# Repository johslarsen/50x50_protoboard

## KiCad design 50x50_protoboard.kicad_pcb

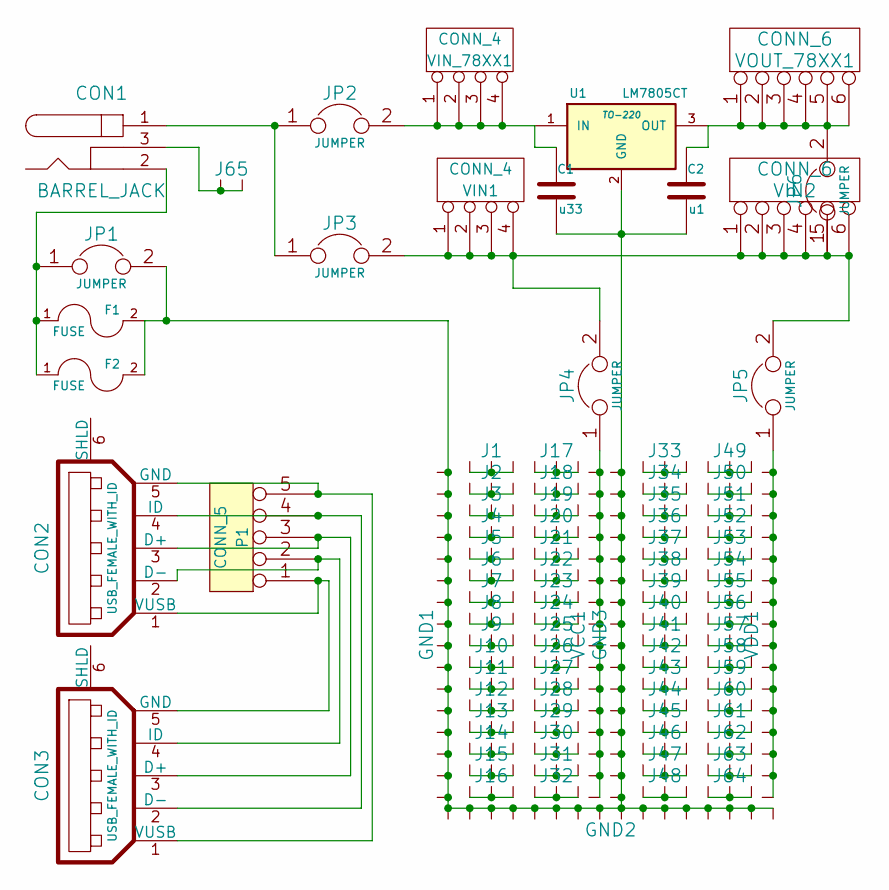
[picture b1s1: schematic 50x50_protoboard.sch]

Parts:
C1: u33
C2: u1
CON1: BARREL_JACK
CON2, CON3: USB_FEMALE_WITH_ID
F1, F2: FUSE
GND1, GND2, GND3: INTERCONNECT_16X1
J1, J2, J3, J4, J5, J6, J7, J8, J9, J10, J11, J12, J13, J14, J15, J16, J17, J18, J19, J20, J21, J22, J23, J24, J25, J26, J27, J28, J29, J30, J31, J32, J33, J34, J35, J36, J37, J38, J39, J40, J41, J42, J43, J44, J45, J46, J47, J48, J49, J50, J51, J52, J53, J54, J55, J56, J57, J58, J59, J60, J61, J62, J63, J64: INTERCONNECT_3X1
J65: INTERCONNECT_2X1
JP1, JP2, JP3, JP4, JP5, JP6: JUMPER
P1: CONN_5
U1: LM7805CT; TO-220
VCC1: INTERCONNECT_16X1
VDD1: INTERCONNECT_16X1
VIN1: CONN_4
VIN2: CONN_6
VIN_78XX1: CONN_4
VOUT_78XX1: CONN_6

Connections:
unnamed: C1.1, JP2.2, U1.1 (IN), VIN_78XX1.1, VIN_78XX1.2, VIN_78XX1.3, VIN_78XX1.4
unnamed: C1.2, C2.2, F1.2, F2.2, GND1.1, GND2.1, GND3.1, JP1.2, U1.2 (GND)
unnamed: C2.1, JP6.2, U1.3 (OUT), VOUT_78XX1.1, VOUT_78XX1.2, VOUT_78XX1.3, VOUT_78XX1.4, VOUT_78XX1.5, VOUT_78XX1.6
unnamed: CON1.1, JP2.1, JP3.1
unnamed: CON1.2, F1.1, F2.1, JP1.1
unnamed: CON1.3, J65.1
unnamed: CON2.1 (VUSB), CON3.5 (GND), P1.1
unnamed: CON2.2 (D-), CON3.4 (ID), P1.2
unnamed: CON2.3 (D+), CON3.3 (D+), P1.3
unnamed: CON2.4 (ID), CON3.2 (D-), P1.4
unnamed: CON2.5 (GND), CON3.1 (VUSB), P1.5
unnamed: JP3.2, JP4.2, JP5.2, JP6.1, VIN1.1, VIN1.2, VIN1.3, VIN1.4, VIN2.1, VIN2.2, VIN2.3, VIN2.4, VIN2.5, VIN2.6
unnamed: JP4.1, VCC1.1
unnamed: JP5.1, VDD1.1

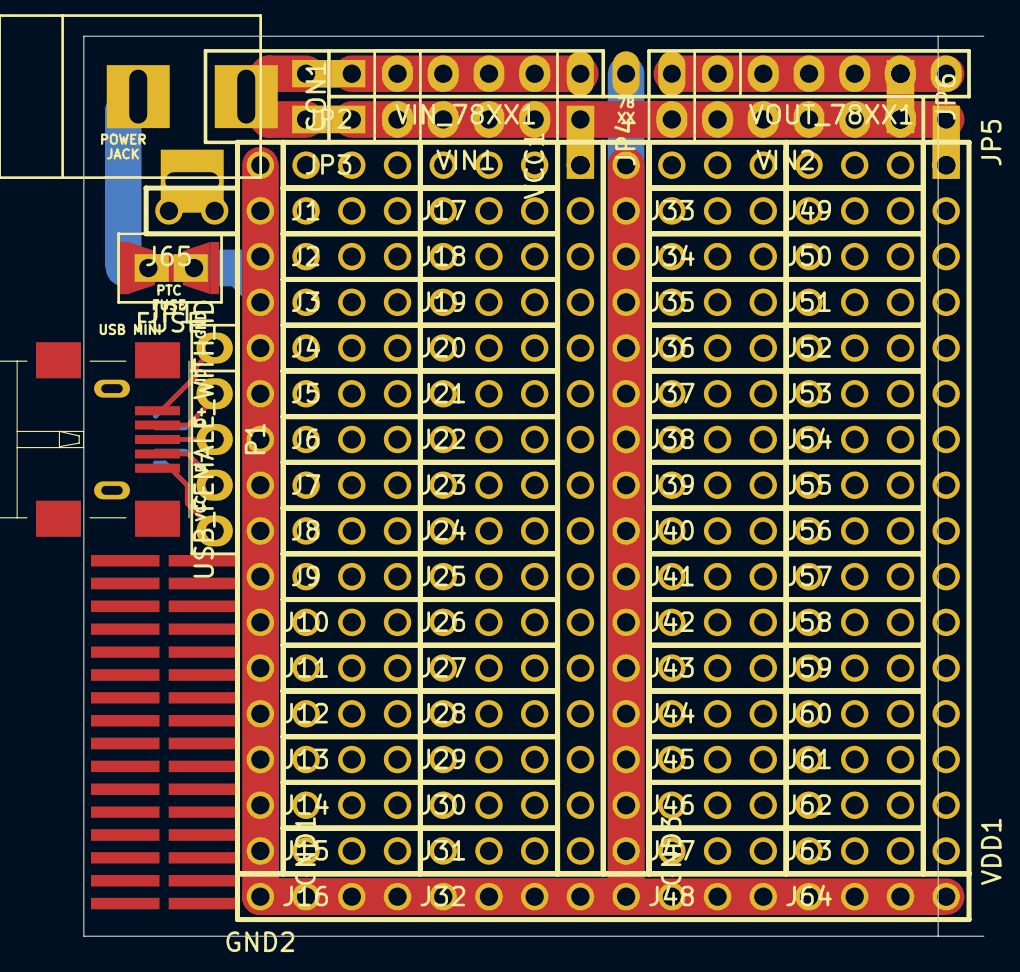
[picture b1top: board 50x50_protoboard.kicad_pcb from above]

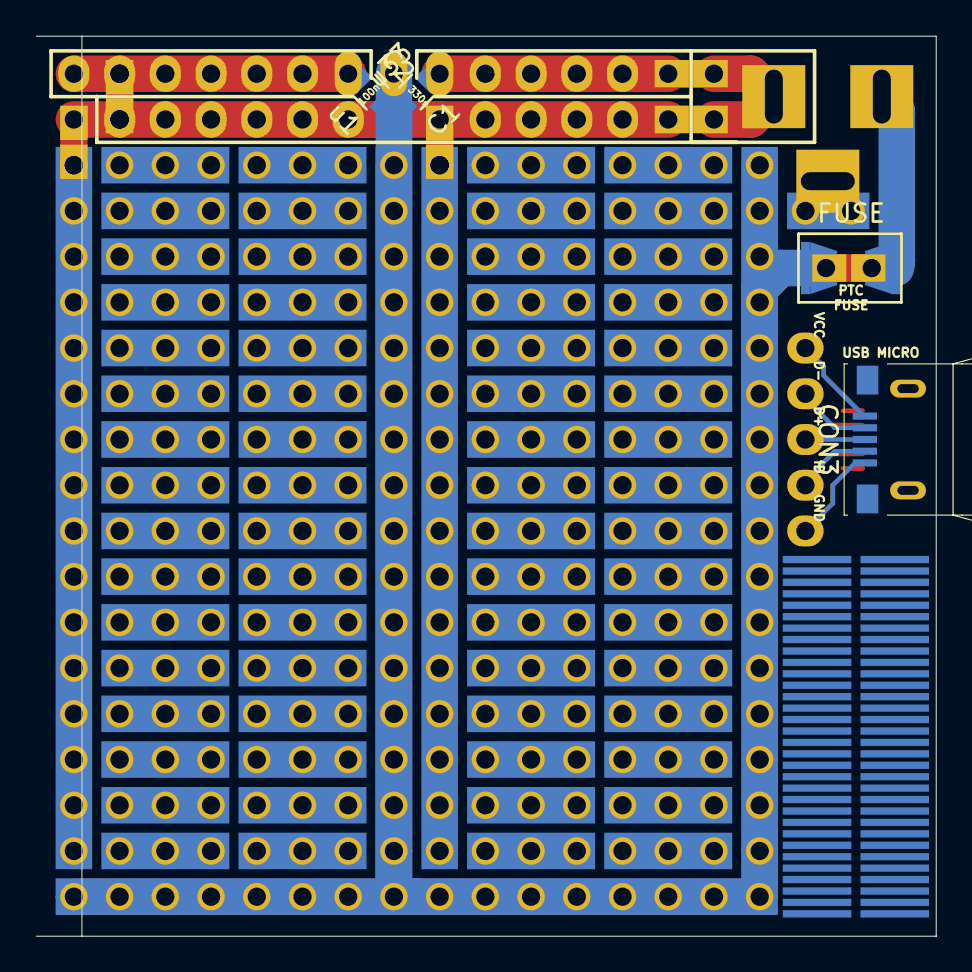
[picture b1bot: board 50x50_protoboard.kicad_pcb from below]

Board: 2 copper layers, 50.0 x 50.0 mm, 95 parts (8 on the bottom side), 14 nets.

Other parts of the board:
Ref**: Val**; SMD_127_381_8X2
Ref**#2: Val**; SMD_127_381_8X2
Ref**#3, Ref**#4, Ref**#5, Ref**#6: Val**; SMD_065_381_8X2

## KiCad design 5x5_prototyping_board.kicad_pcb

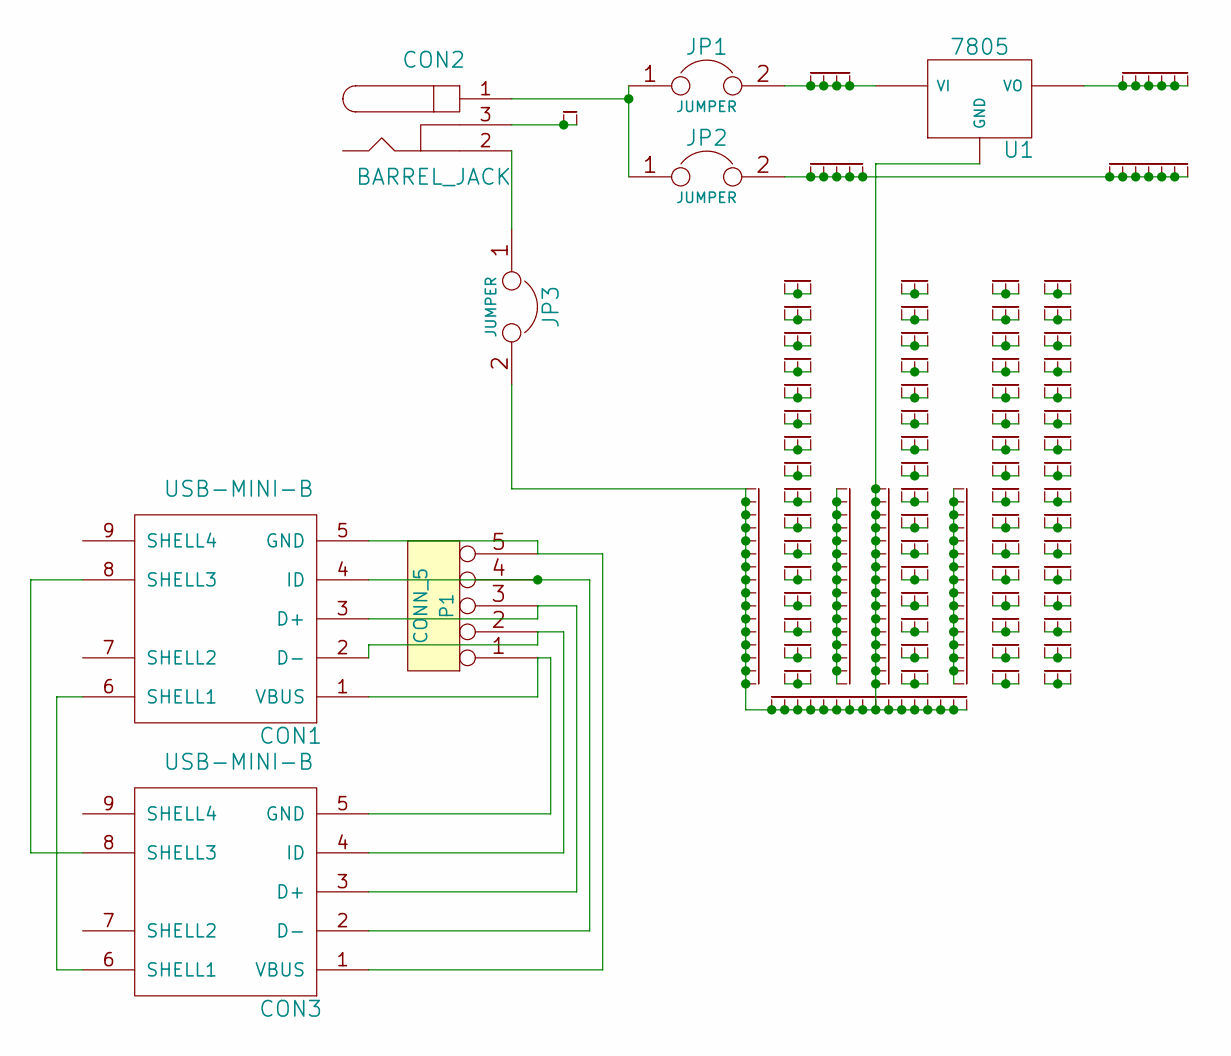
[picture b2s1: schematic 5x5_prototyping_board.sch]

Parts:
CON1, CON3: USB-MINI-B
CON2: BARREL_JACK
J1: INTERCONNECT_2
J2: INTERCONNECT_16_2_16
J3, J4, J5, J6, J7, J8, J9, J10, J11, J12, J13, J14, J15, J16, J17, J18, J22, J23, J24, J25, J26, J27, J28, J29, J30, J31, J32, J33, J34, J35, J36, J37, J41, J42, J43, J44, J45, J46, J47, J48, J49, J50, J51, J52, J53, J54, J55, J56, J57, J58, J59, J60, J61, J62, J63, J64, J65, J66, J67, J68, J69, J70, J71, J72: INTERCONNECT_3
J19: INTERCONNECT_4
J20: INTERCONNECT_5
J21, J38: INTERCONNECT_16
J39: INTERCONNECT_6
J40: INTERCONNECT_7
JP1, JP2, JP3: JUMPER
P1: CONN_5
U1: 7805

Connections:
unnamed: CON2.1, JP1.1, JP2.1
unnamed: CON1.1 (VBUS), CON3.5 (GND), P1.1
unnamed: CON1.2 (D-), CON3.4 (ID), P1.2
unnamed: CON1.3 (D+), CON3.3 (D+), P1.3
unnamed: CON1.5 (GND), CON3.1 (VBUS), P1.5
unnamed: CON1.6 (SHELL1), CON3.6 (SHELL1)
unnamed: CON1.8 (SHELL3), CON3.8 (SHELL3)
unnamed: CON2.2, JP3.1
unnamed: J39.1, J39.2, J39.3, J39.4, J39.5, J39.6, U1.VO
unnamed: J20.1, J20.2, J20.3, J20.4, J20.5, J40.1, J40.2, J40.3, J40.4, J40.5, J40.6, J40.7, JP2.2
unnamed: J19.1, J19.2, J19.3, J19.4, JP1.2, U1.VI
unnamed: J33.1, J33.2, J33.3
unnamed: J32.1, J32.2, J32.3
unnamed: J31.1, J31.2, J31.3
unnamed: J30.1, J30.2, J30.3
unnamed: J38.1, J38.2, J38.3, J38.4, J38.5, J38.6, J38.7, J38.8, J38.9, J38.10, J38.11, J38.12, J38.13, J38.14, J38.15, J38.16
unnamed: J23.1, J23.2, J23.3
unnamed: J22.1, J22.2, J22.3
unnamed: J18.1, J18.2, J18.3
unnamed: J17.1, J17.2, J17.3
unnamed: J16.1, J16.2, J16.3
unnamed: J15.1, J15.2, J15.3
unnamed: J29.1, J29.2, J29.3
unnamed: J28.1, J28.2, J28.3
unnamed: J27.1, J27.2, J27.3
unnamed: J26.1, J26.2, J26.3
unnamed: J25.1, J25.2, J25.3
unnamed: J24.1, J24.2, J24.3
unnamed: J34.1, J34.2, J34.3
unnamed: J2.1, J2.2, J2.3, J2.4, J2.5, J2.6, J2.7, J2.8, J2.9, J2.10, J2.11, J2.12, J2.13, J2.14, J2.15, J2.16, J2.17, J2.18, J2.19, J2.20, J2.21, J2.22, J2.23, J2.24, J2.25, J2.26, J2.27, J2.28, J2.29, J2.30, J2.31, J2.32, J2.33, J2.34, J2.35, J2.36, J2.37, J2.38, J2.39, J2.40, J2.41, J2.42, J2.43, J2.44, J2.45, J2.46, J2.47, J2.48, JP3.2, U1.GND
unnamed: J37.1, J37.2, J37.3
unnamed: J36.1, J36.2, J36.3
unnamed: J35.1, J35.2, J35.3
unnamed: J21.1, J21.2, J21.3, J21.4, J21.5, J21.6, J21.7, J21.8, J21.9, J21.10, J21.11, J21.12, J21.13, J21.14, J21.15, J21.16
unnamed: J71.1, J71.2, J71.3
unnamed: J42.1, J42.2, J42.3
unnamed: J41.1, J41.2, J41.3
unnamed: J72.1, J72.2, J72.3
unnamed: J70.1, J70.2, J70.3
unnamed: J69.1, J69.2, J69.3
unnamed: J48.1, J48.2, J48.3
unnamed: J47.1, J47.2, J47.3
unnamed: J46.1, J46.2, J46.3
unnamed: J68.1, J68.2, J68.3
unnamed: J45.1, J45.2, J45.3
unnamed: J44.1, J44.2, J44.3
unnamed: J43.1, J43.2, J43.3
unnamed: J61.1, J61.2, J61.3
unnamed: J60.1, J60.2, J60.3
unnamed: J59.1, J59.2, J59.3
unnamed: J62.1, J62.2, J62.3
unnamed: J58.1, J58.2, J58.3
unnamed: J57.1, J57.2, J57.3
unnamed: J65.1, J65.2, J65.3
unnamed: J67.1, J67.2, J67.3
unnamed: J66.1, J66.2, J66.3
unnamed: J64.1, J64.2, J64.3
unnamed: J63.1, J63.2, J63.3
unnamed: J7.1, J7.2, J7.3
unnamed: J6.1, J6.2, J6.3
unnamed: J5.1, J5.2, J5.3
unnamed: J8.1, J8.2, J8.3
unnamed: J4.1, J4.2, J4.3
unnamed: J3.1, J3.2, J3.3
unnamed: CON2.3, J1.1, J1.2
unnamed: J11.1, J11.2, J11.3
unnamed: J14.1, J14.2, J14.3
unnamed: J13.1, J13.2, J13.3
unnamed: J12.1, J12.2, J12.3
unnamed: J10.1, J10.2, J10.3
unnamed: J9.1, J9.2, J9.3
unnamed: J54.1, J54.2, J54.3
unnamed: J53.1, J53.2, J53.3
unnamed: J52.1, J52.2, J52.3
unnamed: J55.1, J55.2, J55.3
unnamed: J51.1, J51.2, J51.3
unnamed: J50.1, J50.2, J50.3
unnamed: J49.1, J49.2, J49.3
unnamed: CON1.4 (ID), CON3.2 (D-), P1.4
unnamed: J56.1, J56.2, J56.3

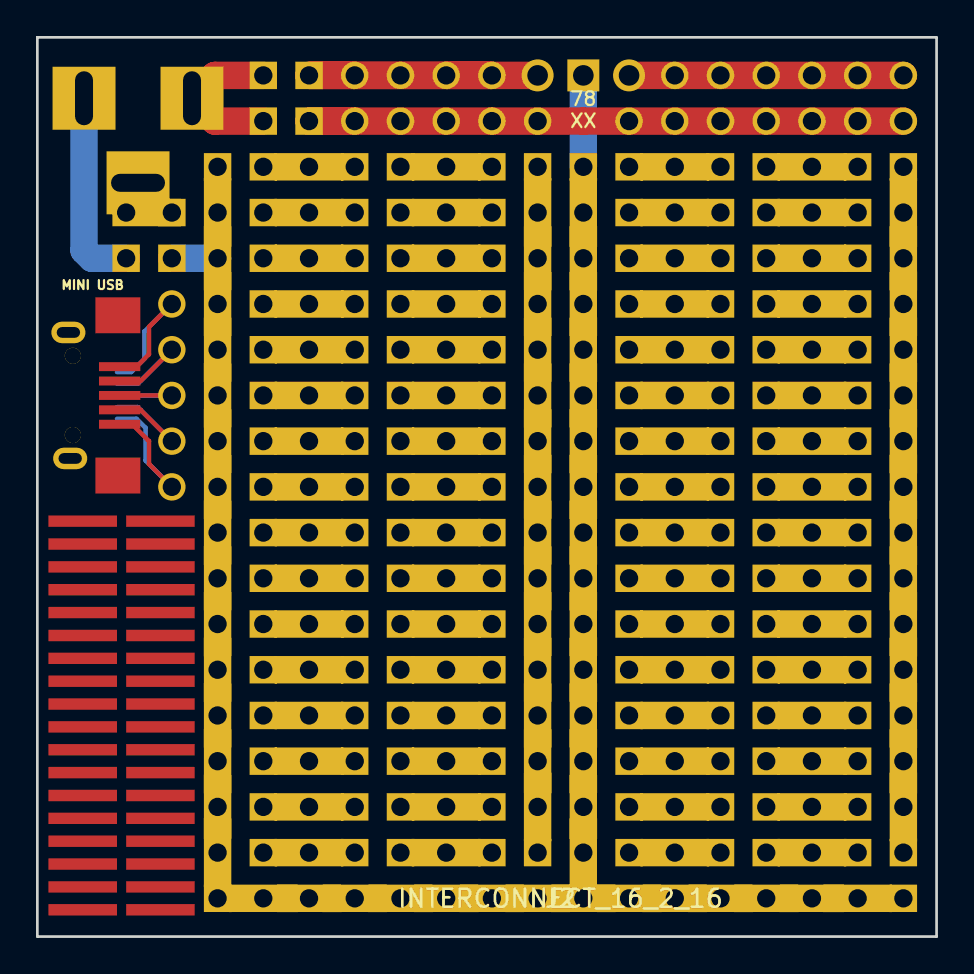
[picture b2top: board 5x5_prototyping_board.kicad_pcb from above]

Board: 2 copper layers, 50.0 x 50.0 mm, 80 parts (1 on the bottom side), 80 nets.

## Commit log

2014-08-02 initial commit, board already sent to printing at dirtypcbs.com
2014-08-02 ignore gerber output
2014-08-02 fixed SMD pin spacing and pad width
2014-08-02 renamed to 5x5_prototyping_board
2014-08-02 fixed some solder mask that had been shifted, probably elements hidden or otherwise ignored whilst moving other components
2014-08-02 added library submodule
2014-08-03 recreated board from scratch and updated lib
2014-08-03 added pads for PTC 1812(SMD) fuse on both sides of the PCB between GND and the barrel jack on the same spot as the jumper and in parallel with it and eachother
2014-08-03 ignored versioned Gerber dirs
2014-08-03 fixed SMD 1.27mm alignment and removed some accidental text on F.Mask
2014-08-04 fixed usb pin header alignment to the other pads and the added traces to both sides of the interconnects
2014-08-04 5x5_protoboard_v1.zip: the v1 Gerber files sent to the board house
2014-08-23 moved submodule lib_kicad to github
2014-08-23 updated submodule lib_kicad to move dangerous prototypes submodule to github
2014-08-27 recreated board using interconnect modules increased rails/triplet pad size, added solder jumper in addition to pin jumpers and added text for USB micro/mini pinout
2014-08-28 created silk screen markings for power rails
2014-08-28 added 0603 suppersion caps to 78xx regulator
2014-08-29 added v1.1 gerbers sent to board house
2014-08-31 fixed bug where gnd rails where only connected on the front of the pcb
2014-09-07 moved gerbers into gerbers subdirectory
2014-09-11 added public domain license
2014-09-21 changed interconnect to only have exposed copper on the bottom side, and shorted the jumper on the front side
2014-09-26 added gerbers for v1.2 and v2
2015-05-07 renamed project to use mm dimensions, so 50x50 instead of 5x5
2015-05-07 switched to UNLICENSE and updated modules and directory structure to that of newer kicad projects
2015-05-08 added screw hole, moved fuse to VIN instead of GND and rounded the outline corners
2015-05-08 added gerbers for v2.1
2015-05-08 created interconnect schematic symbols in 2.54mm_Pin_Headers.pretty
2015-05-08 added missing connection between GND rails and 7805 GND pin
